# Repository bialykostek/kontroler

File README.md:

# Neural controller for Unmanned Aerial Vehicle control
Official repositiry 

List of most important files:

- [jan_kostecki_praca_inzynierska.pdf](/praca/jan_kostecki_praca_inzynierska.pdf) - Engineering Thesis
- [flight_model_18.h](/Kontroler/babyDodoTFPPM/flight_model_18.h) - best AI model (2 minutes in the air!)
- [flight.py](/AI/sintest.py) - Tensorflow model training
- [nettocpp.m](/AI/nettocpp.m) - matlab neural network to C++ converter
- [groundStation.ino](/Ground%20Station/groundStation/groundStation.ino) - ground station software
- [websockeetCOM.py](/Ground%20Station/websocketCOM.py) - relay app
- [babyDodo.ino](/Kontroler/babyDodo/babyDodo.ino) - controller software
- [plytka.kicad_pcb](/plytka/plytka/plytka.kicad_pcb) - PCB design
- [dodo.xfl](/samolot/dodo.xfl) - XFLR5 plane design
- [websocket.js](/serwer/websocket.js) - server software
- [main.html](/webapp/main.html) - web app main page
- [documentation.txt](/documentation.md) - communication protocol documentation

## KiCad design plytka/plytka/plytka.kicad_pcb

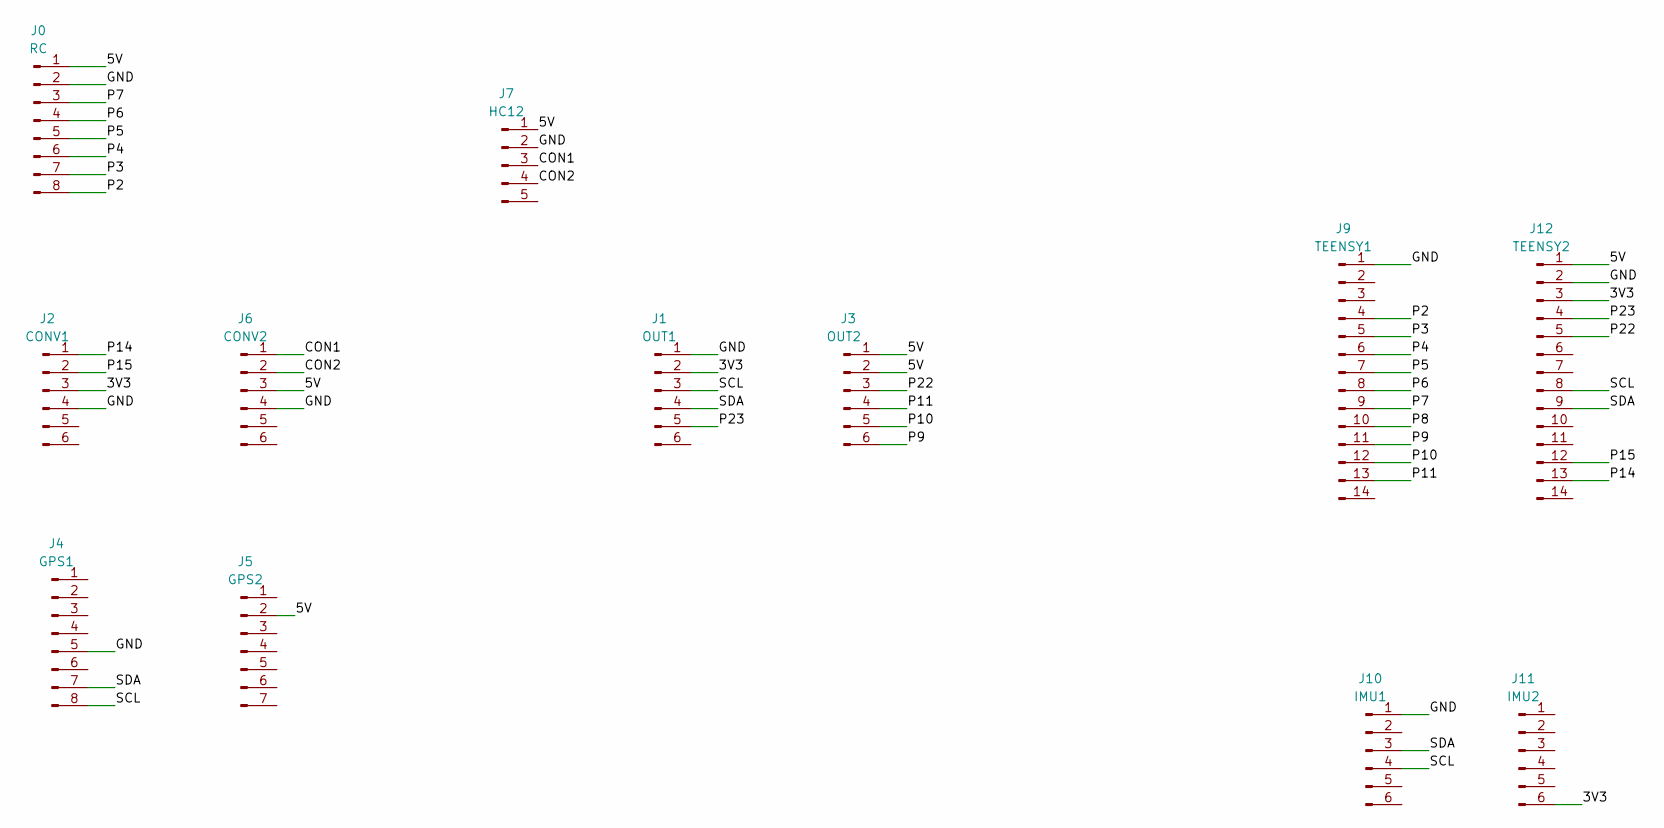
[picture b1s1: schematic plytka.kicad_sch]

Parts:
J0: RC; PinSocket_1x08_P2.54mm_Vertical
J1: OUT1; PinSocket_1x06_P2.54mm_Vertical
J2: CONV1; PinSocket_1x06_P2.54mm_Vertical
J3: OUT2; PinSocket_1x06_P2.54mm_Vertical
J4: GPS1; PinSocket_1x08_P2.54mm_Vertical
J5: GPS2; PinSocket_1x07_P2.54mm_Vertical
J6: CONV2; PinSocket_1x06_P2.54mm_Vertical
J7: HC12; PinSocket_1x05_P2.54mm_Vertical
J9: TEENSY1; PinSocket_1x14_P2.54mm_Vertical
J10: IMU1; PinSocket_1x06_P2.54mm_Vertical
J11: IMU2; PinSocket_1x06_P2.54mm_Vertical
J12: TEENSY2; PinSocket_1x14_P2.54mm_Vertical

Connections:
/3V3: J1.2, J2.3, J11.6, J12.3
/5V: J0.1, J3.1, J3.2, J5.2, J6.3, J7.1, J12.1
/CON1: J6.1, J7.3
/CON2: J6.2, J7.4
/GND: J0.2, J1.1, J2.4, J4.5, J6.4, J7.2, J9.1, J10.1, J12.2
/P2: J0.8, J9.4
/P3: J0.7, J9.5
/P4: J0.6, J9.6
/P5: J0.5, J9.7
/P6: J0.4, J9.8
/P7: J0.3, J9.9
/P8: J9.10
/P9: J3.6, J9.11
/P10: J3.5, J9.12
/P11: J3.4, J9.13
/P14: J2.1, J12.13
/P15: J2.2, J12.12
/P22: J3.3, J12.5
/P23: J1.5, J12.4
/SCL: J1.3, J4.8, J10.4, J12.8
/SDA: J1.4, J4.7, J10.3, J12.9

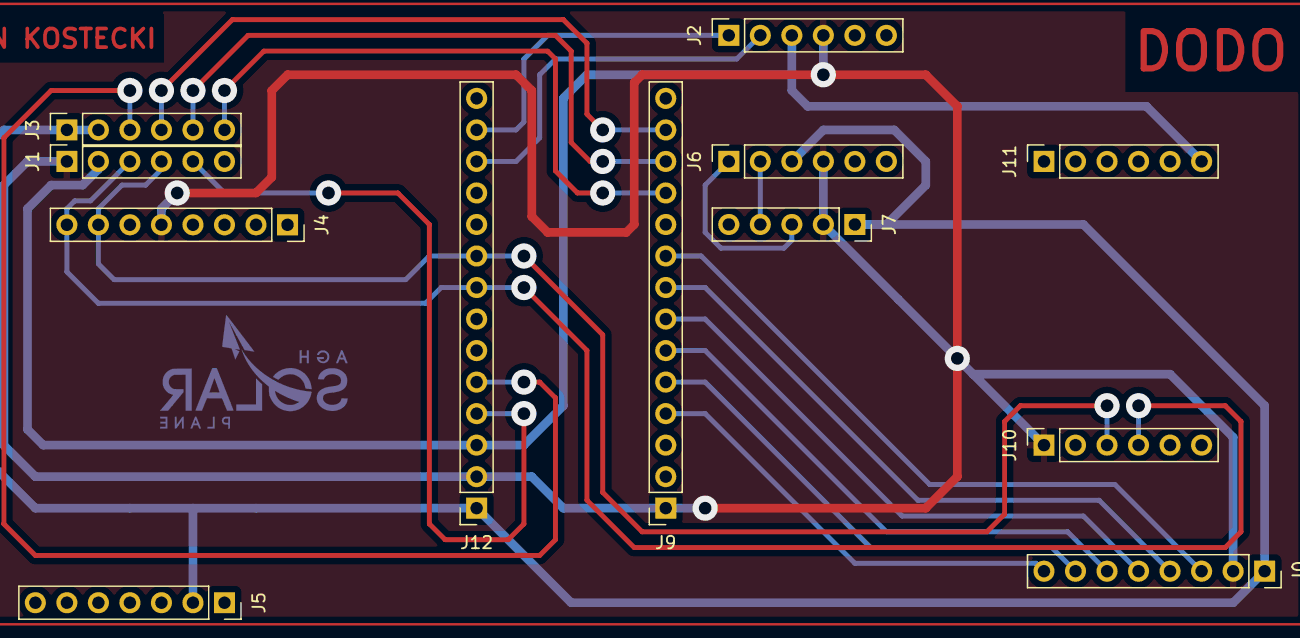
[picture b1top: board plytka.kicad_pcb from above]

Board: 2 copper layers, 13 parts (0 on the bottom side), 20 nets.

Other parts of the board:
Ge: LOGO; LogoSolar_15x9

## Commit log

2022-09-30 Connection to controler
2022-09-30 clean mess
2022-10-01 echo
2022-10-03 live data
2022-10-03 first charts
2022-10-03 imu and gps
2022-10-03 all sensors
2022-10-04 saving files
2022-10-05 visualization and map
2022-10-05 fixed maps transformation
2022-10-08 waypoints
2022-10-09 fixed i2c
2022-10-09 dmp fixed
2022-10-10 radio wtf are you doing
2022-10-17 math on map working
2022-10-22 ready to flight
2022-10-23 player
2022-10-23 preparation for AI
2022-10-28 AI module implemented
2022-11-09 WOW IT FLIES
2022-12-01 well xd commit time
2022-12-04 a lot of text
2022-12-05 more text :)
2022-12-06 few more nights to go
2022-12-13 implementation description done
2022-12-21 first paper fixes
2022-12-22 theory almost done
2022-12-23 added more AI description
2022-12-28 Final veersion & server code
2023-01-05 final cleanup
2023-01-05 more cleanup
2023-06-27 dodo learned flying
2023-06-27 readme update
2025-04-13 commit after long time so no idea
2025-04-18 dodo master
